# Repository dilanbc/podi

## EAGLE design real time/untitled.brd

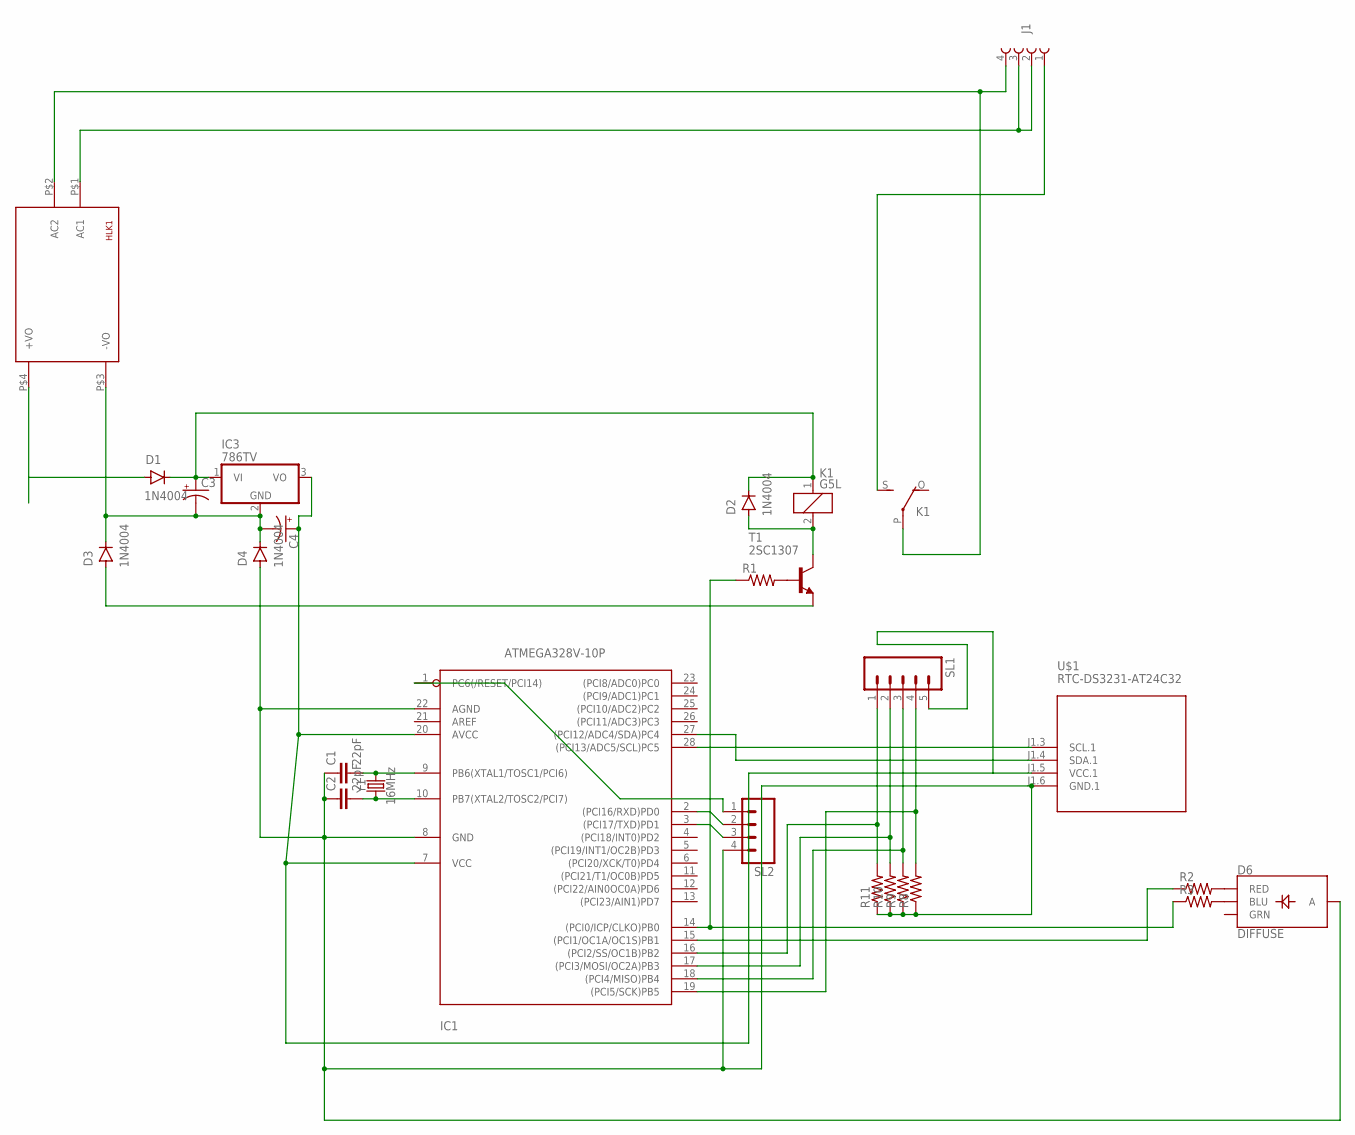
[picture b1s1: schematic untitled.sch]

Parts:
C1, C2: 22pF; CAP-PTH-2.54
C3, C4: CPOL-USE2-4; E2-4
D1, D2, D3, D4: 1N4004; DO-41
D6: DIFFUSE; LED-RGB-THRU
HLK1: HLK-PM013W; HLK-PM01
IC1: ATMEGA328V-10P; DIL28-3
IC3: 786TV; TO220V
J1: 691213500004
K1: G5L; G5LE
R1, R2, R3, R8, R9, R10, R11: R-US_0207/12; 0207/12
SL1: M05; 05P
SL2: M04; 04P
T1: 2SC1307; TO220AV
U$1: RTC-DS3231-AT24C32
Y1: 16MHz; HC49US

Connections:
unnamed: D1.A, HLK1.P$4 (+VO)
unnamed: C3.-, C4.-, D3.C, D4.C, HLK1.P$3 (-VO), IC3.2 (GND)
unnamed: C3.+, D1.C, D2.C, IC3.1 (VI), K1.1
unnamed: C1.2, IC1.9 (PB6(XTAL1/TOSC1/PCI6)), Y1.2
unnamed: C4.+, IC1.7 (VCC), IC1.20 (AVCC), IC3.3 (VO), SL1.5, U$1.J1.5 (VCC.1)
unnamed: C2.2, IC1.10 (PB7(XTAL2/TOSC2/PCI7)), Y1.1
unnamed: IC1.19 ((PCI5/SCK)PB5), R8.2, SL1.4
unnamed: D2.A, K1.2, T1.2 (C)
unnamed: IC1.27 ((PCI12/ADC4/SDA)PC4), U$1.J1.4 (SDA.1)
unnamed: IC1.28 ((PCI13/ADC5/SCL)PC5), U$1.J1.3 (SCL.1)
unnamed: R1.2, T1.1 (B)
unnamed: D3.A, T1.3 (E)
unnamed: IC1.14 ((PCI0/ICP/CLKO)PB0), R1.1, R3.1
unnamed: HLK1.P$2 (AC2), J1.4 (1), K1.P
unnamed: HLK1.P$1 (AC1), J1.2 (3), J1.3 (2)
unnamed: D6.1 (RED), R2.2
unnamed: D6.4 (BLU), R3.2
unnamed: J1.1 (4), K1.S
unnamed: IC1.15 ((PCI1/OC1A/OC1S)PB1), R2.1
unnamed: IC1.1 (PC6(/RESET/PCI14)), SL2.1
unnamed: C1.1, C2.1, D4.A, D6.2 (A), IC1.8 (GND), IC1.22 (AGND), R8.1, R9.1, R10.1, R11.1, SL2.4, U$1.J1.6 (GND.1)
unnamed: IC1.18 ((PCI4/MISO)PB4), R9.2, SL1.3
unnamed: IC1.17 ((PCI3/MOSI/OC2A)PB3), R10.2, SL1.2
unnamed: IC1.16 ((PCI2/SS/OC1B)PB2), R11.2, SL1.1
unnamed: IC1.2 ((PCI16/RXD)PD0), SL2.2
unnamed: IC1.3 ((PCI17/TXD)PD1), SL2.3

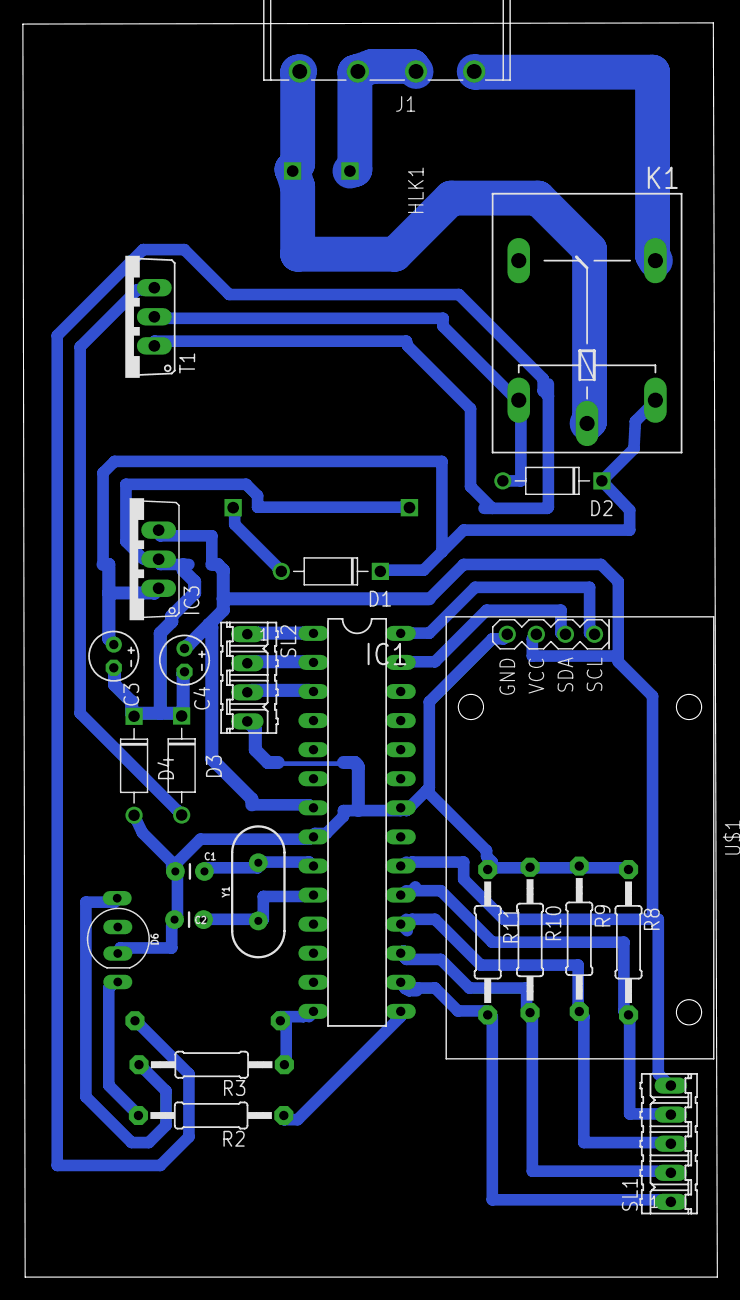
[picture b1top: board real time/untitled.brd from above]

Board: 2 copper layers, 60.7 x 109.6 mm, 26 parts (1 on the bottom side), 26 nets.

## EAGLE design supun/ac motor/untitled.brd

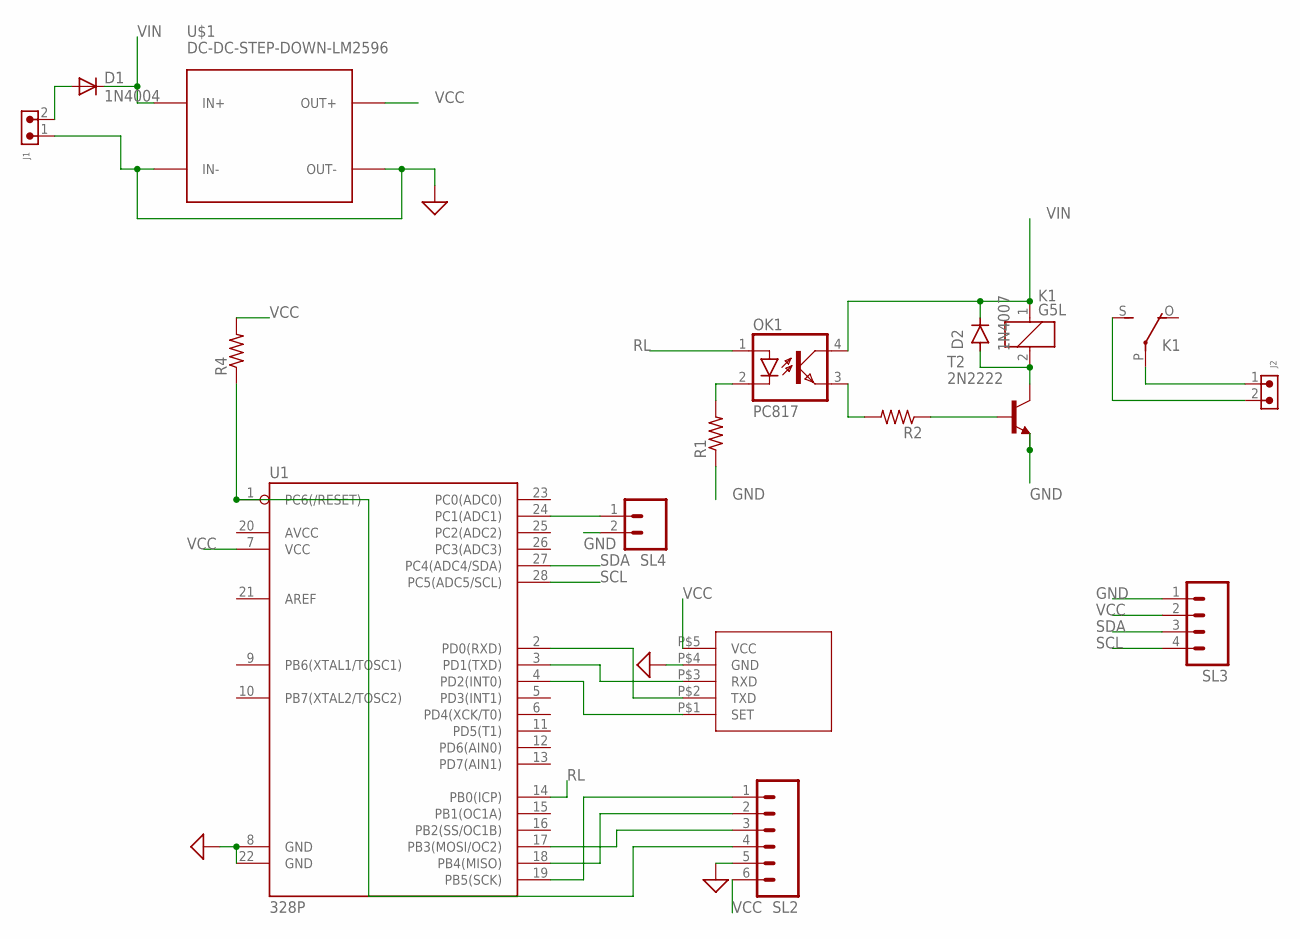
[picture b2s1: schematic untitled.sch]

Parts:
D1: 1N4004; DO41-10
D2: 1N4007; DO-41
J1, J2: 691305530002
K1: G5L; G5LE
OK1: PC817; DIL04
R1, R4: R-US_0207/7; 0207/7
R2: R-US_0207/12; 0207/12
SL2: M06; 06P
SL3: M04; 04P
SL4: M02; 02P
T2: 2N2222; TO92-EBC-OVAL
U1: 328P; DIP28
U$1: DC-DC-STEP-DOWN-LM2596
U$3: HC12

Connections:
GND: J1.1, R1.1, SL2.5, SL3.1, SL4.2, T2.E, U1.8 (GND), U1.22 (GND), U$1.IN-, U$1.OUT-, U$3.P$4 (GND)
unnamed: D1.A, J1.2
unnamed: U1.2 (PD0(RXD)), U$3.P$2 (TXD)
unnamed: SL2.1, U1.19 (PB5(SCK))
unnamed: SL2.2, U1.18 (PB4(MISO))
unnamed: SL2.3, U1.17 (PB3(MOSI/OC2))
unnamed: U1.3 (PD1(TXD)), U$3.P$3 (RXD)
unnamed: U1.4 (PD2(INT0)), U$3.P$1 (SET)
unnamed: R2.1, T2.B
unnamed: D2.A, K1.2, T2.C
unnamed: OK1.2 (C), R1.2
unnamed: J2.1, K1.P
unnamed: OK1.3 (EMIT), R2.2
unnamed: R4.1, SL2.4, U1.1 (PC6(/RESET))
unnamed: SL4.1, U1.24 (PC1(ADC1))
unnamed: J2.2, K1.S
RL: OK1.1 (A), U1.14 (PB0(ICP))
SCL: SL3.4, U1.28 (PC5(ADC5/SCL))
SDA: SL3.3, U1.27 (PC4(ADC4/SDA))
VCC: R4.2, SL2.6, SL3.2, U1.7 (VCC), U$1.OUT+, U$3.P$5 (VCC)
VIN: D1.C, D2.C, K1.1, OK1.4 (COL), U$1.IN+

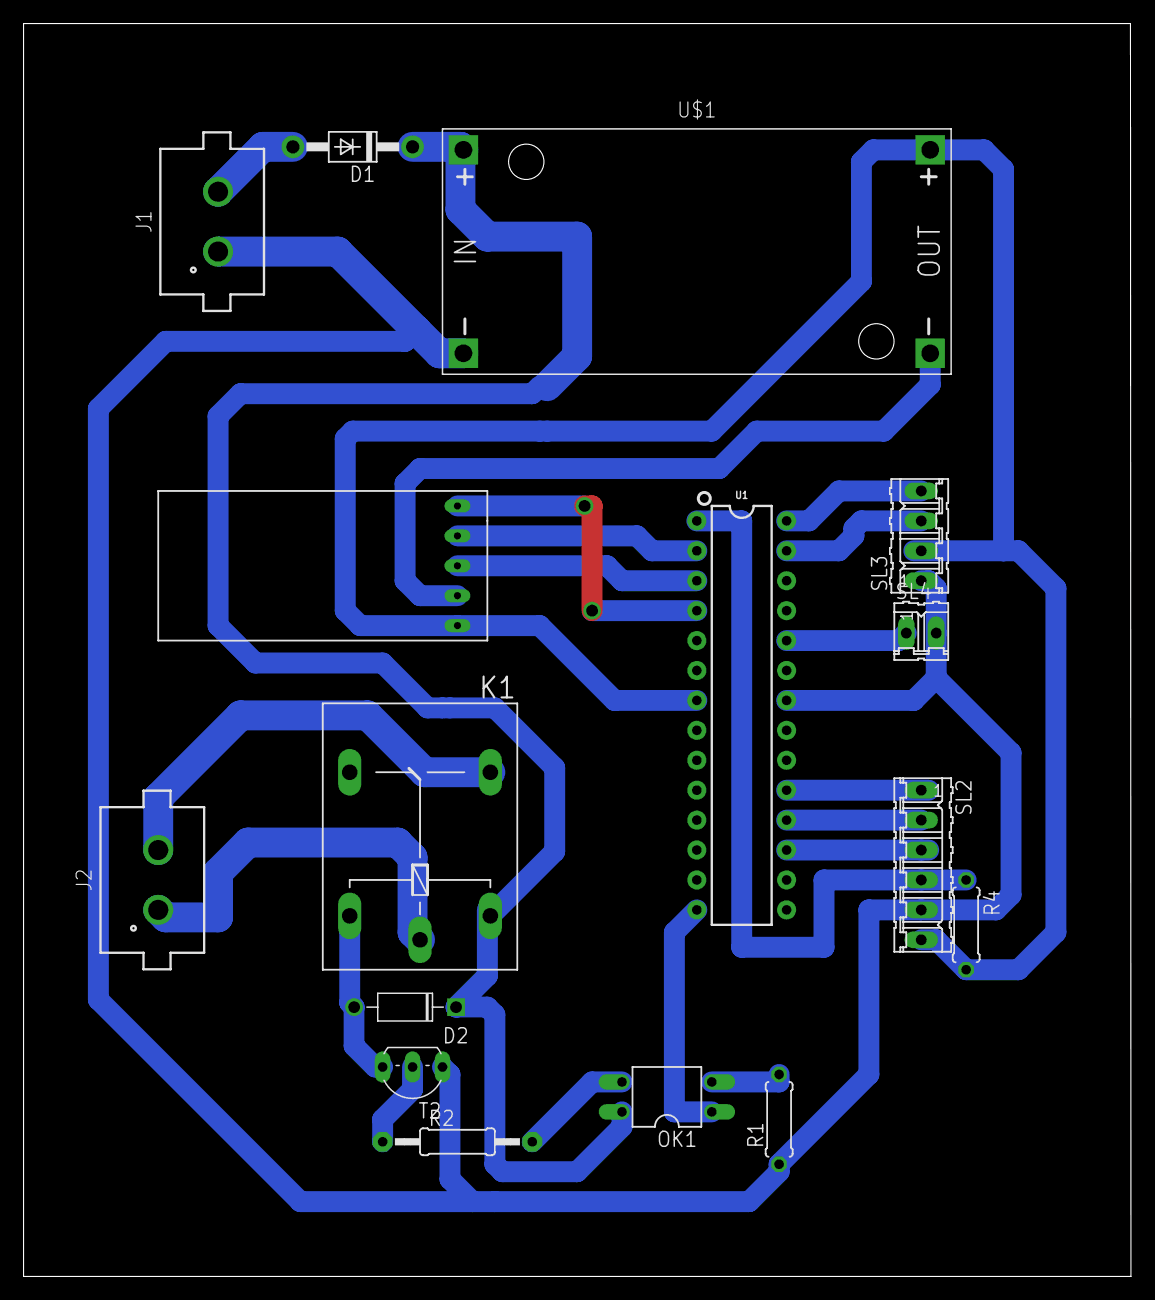
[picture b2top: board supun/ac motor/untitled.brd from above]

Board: 2 copper layers, 94.0 x 106.3 mm, 16 parts (0 on the bottom side), 21 nets.

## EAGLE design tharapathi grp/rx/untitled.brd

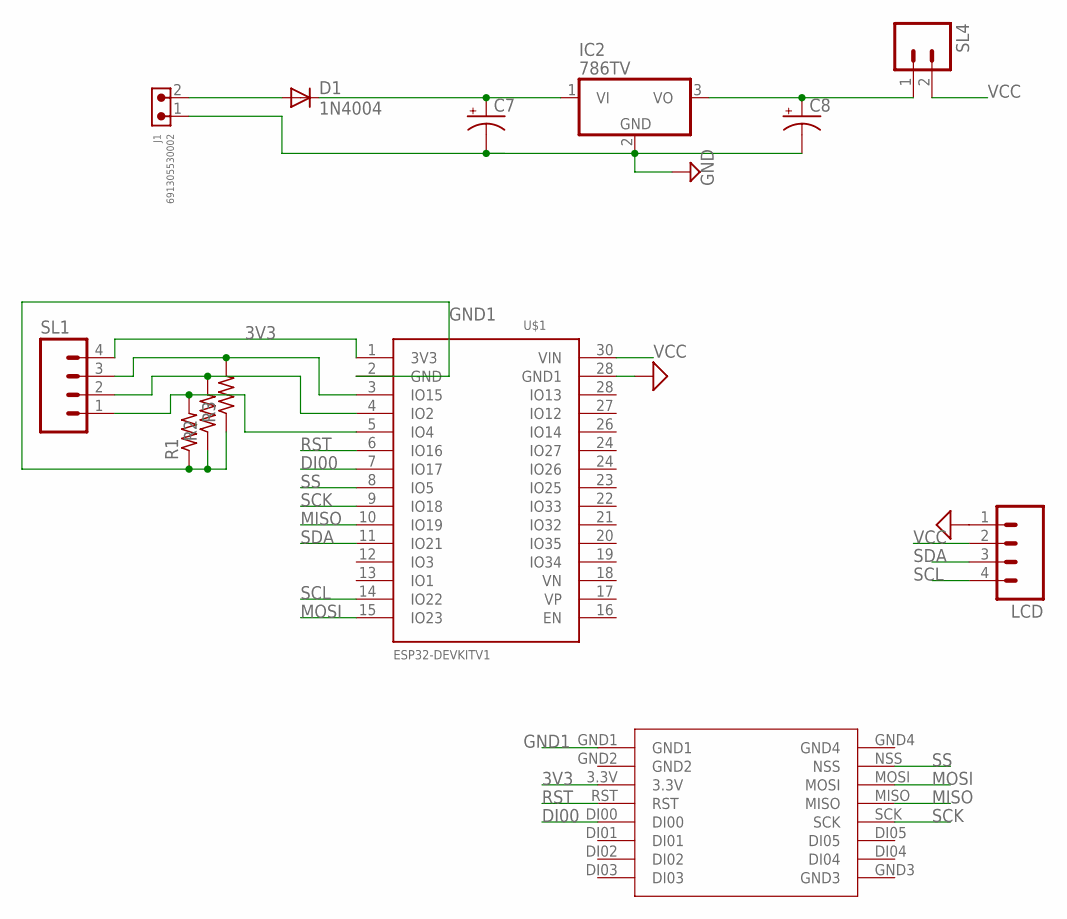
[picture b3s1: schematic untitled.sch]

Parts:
C7: CAPACITOR-PE5-10.5; E5-10,5
C8: CAPACITOR-PE5-6; E5-6
D1: 1N4004; DO41-10
IC2: 786TV; TO220V
J1: 691305530002
LCD: M04; 04P
R1, R2: R-US_0207/10; 0207/10
R3: R-US_0207/7; 0207/7
SL1: M04; 04P
SL4: M02; 02P
U$1: ESP32DEVKITV1; ESP32-DEVKITV1
U$2: LORASX1278

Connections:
3V3: SL1.4, U$1.1 (3V3), U$2.3.3V
DI00: U$1.7 (IO17), U$2.DI00
GND: C7.-, C8.-, IC2.2 (GND), J1.1, LCD.1, U$1.28 (IO13)
GND1: R1.1, R2.1, R3.1, U$1.2 (GND), U$2.GND1
MISO: U$1.10 (IO19), U$2.MISO
MOSI: U$1.15 (IO23), U$2.MOSI
unnamed: D1.A, J1.2
unnamed: C8.+, IC2.3 (VO), SL4.1
unnamed: R1.2, SL1.1, U$1.5 (IO4)
unnamed: R2.2, SL1.2, U$1.4 (IO2)
unnamed: R3.2, SL1.3, U$1.3 (IO15)
RST: U$1.6 (IO16), U$2.RST
SCK: U$1.9 (IO18), U$2.SCK
SCL: LCD.4, U$1.14 (IO22)
SDA: LCD.3, U$1.11 (IO21)
SS: U$1.8 (IO5), U$2.NSS
VCC: LCD.2, SL4.2, U$1.30 (VIN)
VIN: C7.+, D1.C, IC2.1 (VI)

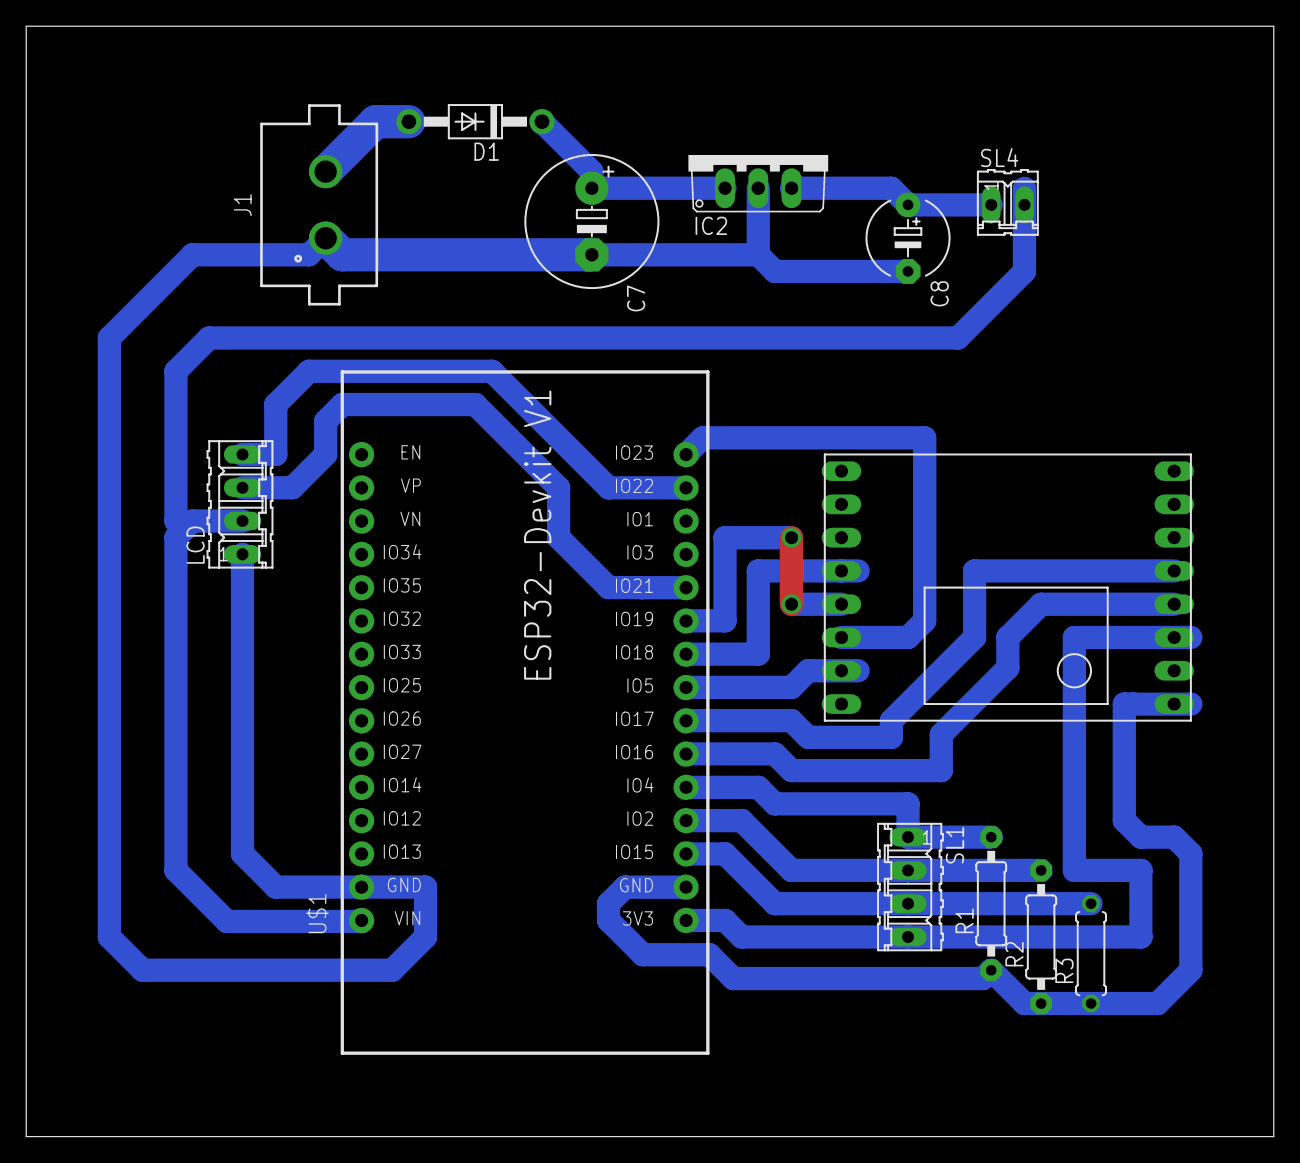
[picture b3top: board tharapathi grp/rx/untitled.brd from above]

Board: 2 copper layers, 95.2 x 84.8 mm, 13 parts (0 on the bottom side), 18 nets.

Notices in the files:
parts and their libraries:
SparkFun-LEDmy: Licensing: Creative Commons ShareAlike 4.0 International - https://creativecommons.org/licenses/by-sa/4.0
Wurth_Elektronik_Electromechanic_Termina: Copyright: Würth Elektronik
